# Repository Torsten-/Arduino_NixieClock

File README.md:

Arduino_NixieClock
==================

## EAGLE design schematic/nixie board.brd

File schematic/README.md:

# Teileliste

Name | Typ | Anzahl | Link
-----|------|--------| -----
. | 12V Power Supply | 1 | 
. | Einbaubuchse für Hohlstecker 5,5/2,1 | 1 | [DC 072341L](https://www.reichelt.de/einbaubuchse-aussen-5-6-mm-innen-2-1-mm-dc-072341l-p196470.html)
. | Nixie Power Supply | 1 | ebay?
N1, N2, N3, N4, N5, N6 | Nixie IN-14 | 6 | ebay?
SR50 | MCP1702-50 | 1 |  [MCP 1702-5002](https://www.reichelt.de/ldo-regler-fest-5-v-to-92-mcp-1702-5002-p90115.html)
SR33 | MCP1702-33 | 1 | [MCP 1702-3302](https://www.reichelt.de/ldo-regler-fest-3-3-v-to-92-mcp-1702-3302-p90114.html)
ESP-07/12 | ESP-07 | 1 | ebay?
IC1<br/>  | SN74141 / K155ID1<br/>IC-Sockel 16-polig | 1<br/>1 | ebay?<br/>[GS 16](https://www.reichelt.de/ic-sockel-16-polig-doppelter-federkontakt-gs-16-p8208.html)
PROG, RESET | Printtaster | 2 | [RND 210-00187](https://www.reichelt.de/printtaster-tht-1-57-n-6-x-6-x-4-3-mm-rnd-210-00187-p226408.html)
POWER | Stiftleiste RM 2,54 1x3-pol | 1 | [SL 1X40G 2,54](https://www.reichelt.de/40pol-stiftleiste-gerade-rm-2-54-sl-1x40g-2-54-p19506.html)
SERIAL | Stiftleiste RM 2,54 1x5-pol | 1 | s.o.
EXT1, EXT2 | Buchsenleiste RM 2,54 1x7-pol | 2 | [BKL 10120802](https://www.reichelt.de/buchsenleiste-36-polig-vergoldet-2-54-bkl-10120802-p235673.html)
NUMBERS<br/> <br/>  | Pfostenbuchse 10P<br/>Wannenstecker 10P<br/>Flachbandkabel 10P | 1<br/>1<br/>1 | [PFL 10](https://www.reichelt.de/pfostenbuchse-10-polig-mit-zugentlastung-pfl-10-p14571.html)<br/>[WSL 10G](https://www.reichelt.de/wannenstecker-10-polig-gerade-wsl-10g-p22816.html)<br/>[AWG 28-16G 3M](https://www.reichelt.de/flachbandkabel-awg28-16-pol-grau-3m-ring-awg-28-16g-3m-p47640.html)
DIGITS<br/> <br/>  | Pfostenbuchse 6P<br/>Wannenstecker 6P<br/>Flachbandkabel 6P | 1<br/>1<br/>1 | [PFL 6](https://www.reichelt.de/pfostenbuchse-6-polig-mit-zugentlastung-pfl-6-p53153.html)<br/>[WSL 6G](https://www.reichelt.de/wannenstecker-6-polig-gerade-wsl-6g-p85732.html)<br/>s.o.
T1, T2, T3, T4, T5, T6 | MPSA42 | 6 | [MPSA 42](https://www.reichelt.de/bipolartransistor-npn-300v-0-5a-0-625w-to-92-mpsa-42-p13112.html)
T7, T8, T9, T10, T11, T12 | MPSA92 | 6 | [MPSA 92](https://www.reichelt.de/bipolartransistor-pnp-300v-0-5a-0-625w-to-92-mpsa-92-p13119.html)
C1, C2, C3, C4 | 1 µF Ceramic | 4 | [Z5U-5 1,0µ](https://www.reichelt.de/vielschicht-keramikkondensator-1-0-20-z5u-5-1-0-p22985.html)
C5 | 100 µF Elko | 1 | [RAD 100/16](https://www.reichelt.de/elko-radial-100-f-16-v-rm-2-5-85-c-2000h-20-rad-100-16-p15101.html)
R1, R2, R3, R4, R5, R6 | 33k | 6 | [1/4W 33K](https://www.reichelt.de/widerstand-kohleschicht-33-kohm-0207-250-mw-5-1-4w-33k-p1412.html)
R7, R8, R9, R10, R11, R12 | 470k | 6 | [1/4W 470K](https://www.reichelt.de/widerstand-kohleschicht-470-kohm-0207-250-mw-5-1-4w-470k-p1433.html)
R13, R14, R15, R16, R17, R18 | 100k | 6 | [1/4W 100K](https://www.reichelt.de/widerstand-kohleschicht-100-kohm-0207-250-mw-5-1-4w-100k-p1337.html)
R19, R20 | 10k | 2 | [1/4W 10K](https://www.reichelt.de/widerstand-kohleschicht-10-kohm-0207-250-mw-5-1-4w-10k-p1338.html)
R101, R102, R103, R104, R105, R106 | 4,7k 1W | 6 | [1W 4,7K](https://www.reichelt.de/widerstand-metalloxyd-4-7-kohm-0207-1-0-w-5-1w-4-7k-p1822.html)

Bohrer für die Nixies: 19 mm

# Belegung Schieberegister
Die Pin-Belegung ist leider etwas durcheinander geraten.

Nixie Ziffer | Kabel Nummer | Schieberegister Ziffer | Schieberegister Pin | Bitmap (DCBA) | Bitmap (ABCD)
-----|-----|-----|-----|-----|-----
0 |  1 | 0 | 16 | 0000 | 0000
9 |  2 | 1 | 15 | 0001 | 1000
8 |  3 | 2 | 8 | 0010 | 0100
7 |  4 | 3 | 9 | 0011 | 1100
6 |  5 | 4 | 13 | 0100 | 0010
5 |  6 | 5 | 14 | 0101 | 1010
4 |  7 | 6 | 11 | 0110 | 0110
3 |  8 | 7 | 10 | 0111 | 1110
2 |  9 | 8 | 1 | 1000 | 0001
1 | 10 | 9 | 2 | 1001 | 1001

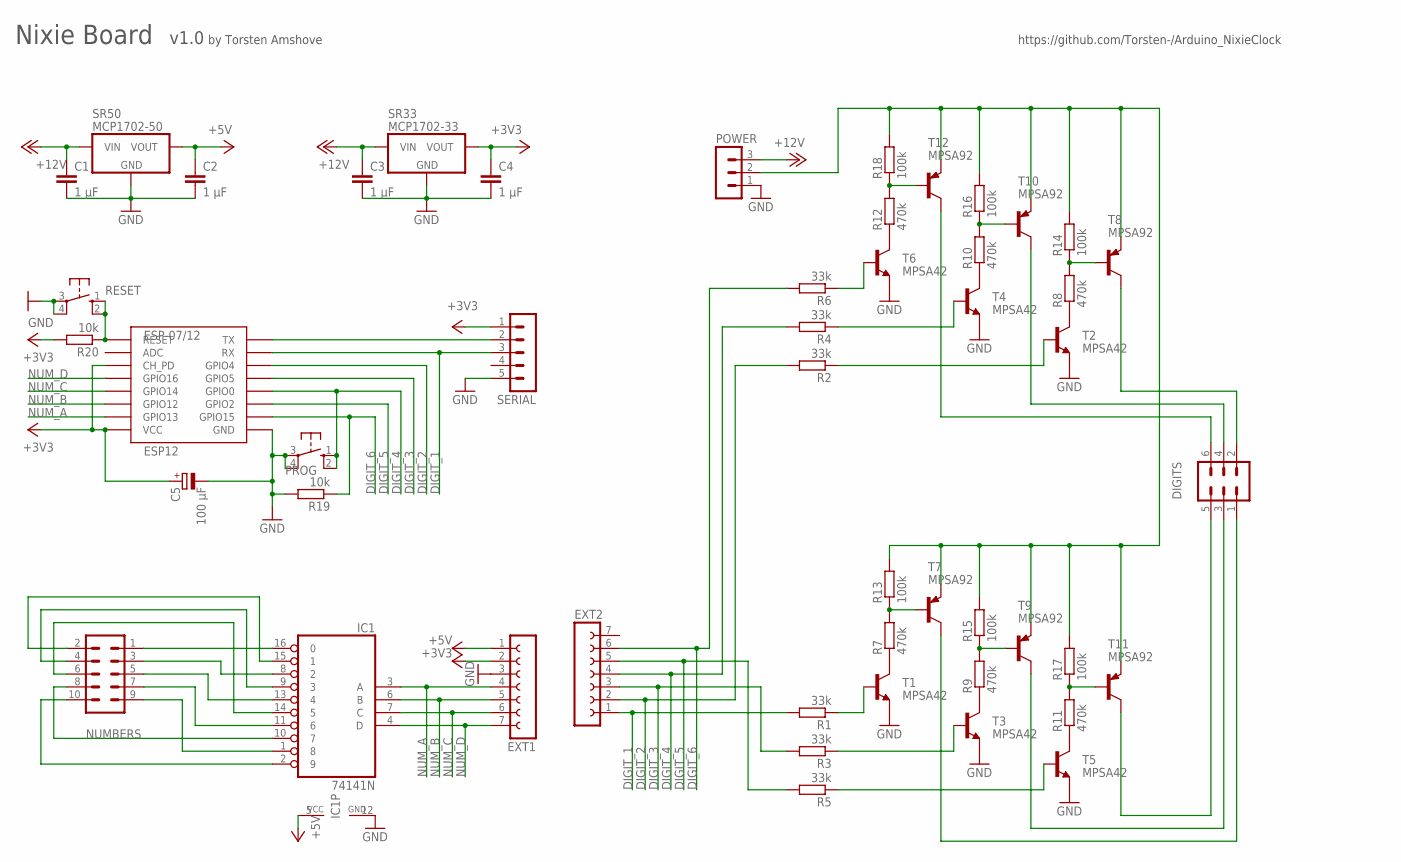
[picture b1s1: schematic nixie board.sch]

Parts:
C1, C2, C3, C4: 1 µF; C5B4.5
C5: 100 µF; E2,5-6
DIGITS: MA03-2
ESP-07/12: ESP12
EXT1, EXT2: FE07-1; FE07
IC1: 74141N; DIL16
NUMBERS: MA05-2
POWER: MA03-1
PROG: 10-XX; B3F-10XX
R1, R2, R3, R4, R5, R6: 33k; 0204/7
R7, R8, R9, R10, R11, R12: 470k; 0204/7
R13, R14, R15, R16, R17, R18: 100k; 0207/2V
R19, R20: 10k; 0204/7
RESET: 10-XX; B3F-10XX
SERIAL: MA05-1
SR33: MCP1702-33; TO-92
SR50: MCP1702-50; TO-92
T1, T2, T3, T4, T5, T6: MPSA42; TO92-EBC
T7, T8, T9, T10, T11, T12: MPSA92; TO92-EBC

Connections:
+3V3: C4.1, C5.+, ESP-07/12.CH_PD, ESP-07/12.VCC, EXT1.2, R20.2, SERIAL.1, SR33.3 (VOUT)
+5V: C2.1, EXT1.1, IC1.5 (VCC), SR50.3 (VOUT)
+12V: C1.1, C3.1, POWER.3, SR33.2 (VIN), SR50.2 (VIN)
DIGIT_1: ESP-07/12.RX, EXT2.1, R1.2, SERIAL.3
DIGIT_2: ESP-07/12.GPIO4, EXT2.2, R2.2
DIGIT_3: ESP-07/12.GPIO5, EXT2.3, R3.2
DIGIT_4: ESP-07/12.GPIO0, EXT2.4, PROG.1 (S), PROG.2 (S1), R4.2
DIGIT_5: ESP-07/12.GPIO2, EXT2.5, R5.2
DIGIT_6: ESP-07/12.GPIO15, EXT2.6, R6.2, R19.1
GND: C1.2, C2.2, C3.2, C4.2, C5.-, ESP-07/12.GND, EXT1.3, IC1.12 (GND), POWER.1, PROG.3, PROG.4 (P1), R19.2, RESET.3, RESET.4 (P1), SERIAL.5, SR33.1 (GND), SR50.1 (GND), T1.E, T2.E, T3.E, T4.E, T5.E, T6.E
unnamed: ESP-07/12.TX, SERIAL.2
unnamed: IC1.16 (0), NUMBERS.1
unnamed: IC1.15 (1), NUMBERS.2
unnamed: POWER.2, R13.2, R14.2, R15.2, R16.2, R17.2, R18.2, T7.E, T8.E, T9.E, T10.E, T11.E, T12.E
unnamed: R6.1, T6.B
unnamed: R4.1, T4.B
unnamed: R12.1, T6.C
unnamed: R12.2, R18.1, T12.B
unnamed: R2.1, T2.B
unnamed: IC1.9 (3), NUMBERS.4
unnamed: IC1.14 (5), NUMBERS.6
unnamed: R10.1, T4.C
unnamed: R10.2, R16.1, T10.B
unnamed: IC1.8 (2), NUMBERS.3
unnamed: DIGITS.6, T12.C
unnamed: R7.1, T1.C
unnamed: R8.1, T2.C
unnamed: R8.2, R14.1, T8.B
unnamed: R7.2, R13.1, T7.B
unnamed: DIGITS.4, T10.C
unnamed: DIGITS.2, T8.C
unnamed: R9.1, T3.C
unnamed: R9.2, R15.1, T9.B
unnamed: IC1.13 (4), NUMBERS.5
unnamed: R11.1, T5.C
unnamed: R11.2, R17.1, T11.B
unnamed: IC1.11 (6), NUMBERS.7
unnamed: IC1.1 (8), NUMBERS.9
unnamed: IC1.10 (7), NUMBERS.8
unnamed: R1.1, T1.B
unnamed: R3.1, T3.B
unnamed: R5.1, T5.B
unnamed: IC1.2 (9), NUMBERS.10
unnamed: ESP-07/12.RESET, R20.1, RESET.1 (S), RESET.2 (S1)
unnamed: DIGITS.5, T11.C
unnamed: DIGITS.3, T9.C
unnamed: DIGITS.1, T7.C
NUM_A: ESP-07/12.GPIO13, EXT1.4, IC1.3 (A)
NUM_B: ESP-07/12.GPIO12, EXT1.5, IC1.6 (B)
NUM_C: ESP-07/12.GPIO14, EXT1.6, IC1.7 (C)
NUM_D: ESP-07/12.GPIO16, EXT1.7, IC1.4 (D)

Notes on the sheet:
Nixie Board
v1.0
https://github.com/Torsten-/Arduino_NixieClock
by Torsten Amshove

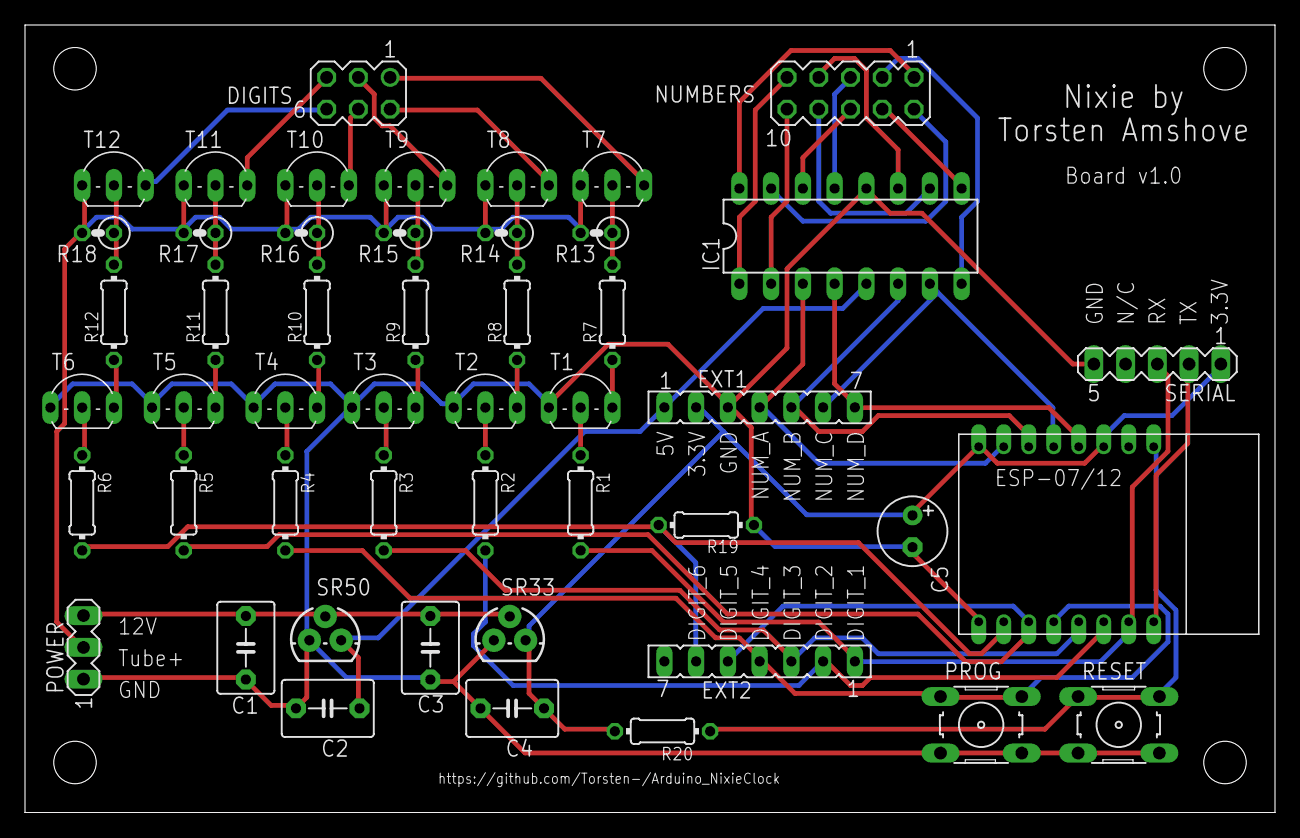
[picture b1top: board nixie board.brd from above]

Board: 2 copper layers, 100.0 x 63.0 mm, 49 parts (0 on the bottom side), 51 nets.

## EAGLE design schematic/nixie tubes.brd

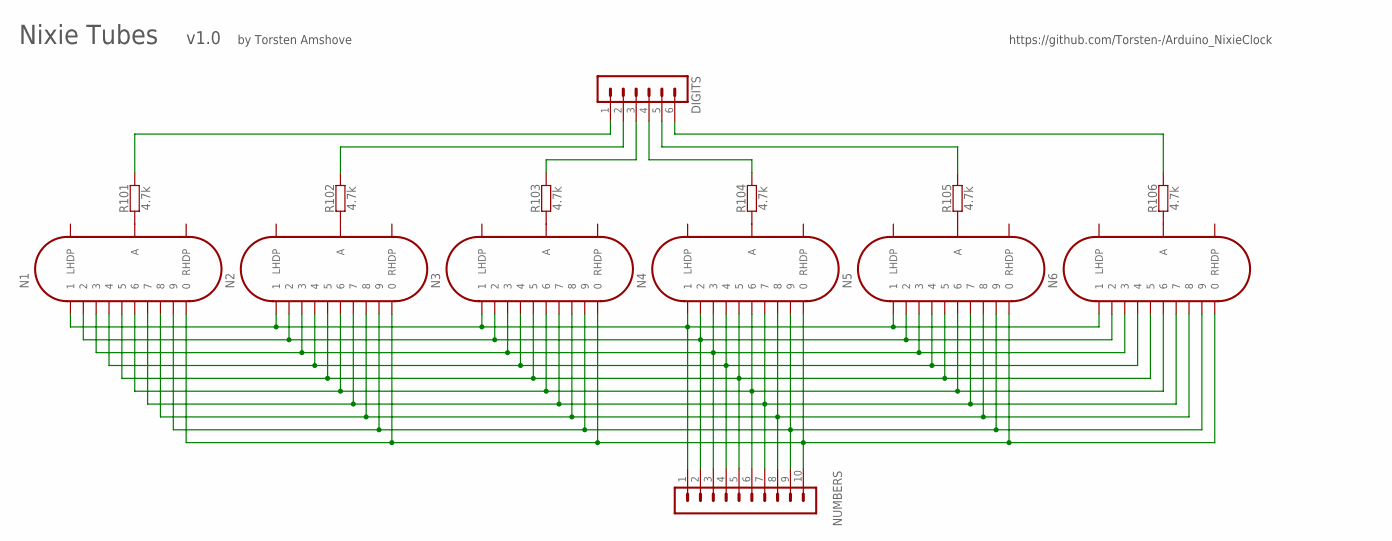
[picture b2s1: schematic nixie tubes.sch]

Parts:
DIGITS: MA06-1
N1, N2, N3, N4, N5, N6: IN-14
NUMBERS: MA10-1
R101, R102, R103, R104, R105, R106: 4.7k; R0207/10

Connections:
unnamed: N1.A, R101.1
unnamed: N2.A, R102.1
unnamed: N3.A, R103.1
unnamed: N4.A, R104.1
unnamed: N5.A, R105.1
unnamed: N6.A, R106.1
unnamed: N1.1, N2.1, N3.1, N4.1, N5.1, N6.1, NUMBERS.1
unnamed: N1.2, N2.2, N3.2, N4.2, N5.2, N6.2, NUMBERS.2
unnamed: N1.3, N2.3, N3.3, N4.3, N5.3, N6.3, NUMBERS.3
unnamed: N1.4, N2.4, N3.4, N4.4, N5.4, N6.4, NUMBERS.4
unnamed: N1.5, N2.5, N3.5, N4.5, N5.5, N6.5, NUMBERS.5
unnamed: N1.6, N2.6, N3.6, N4.6, N5.6, N6.6, NUMBERS.6
unnamed: N1.7, N2.7, N3.7, N4.7, N5.7, N6.7, NUMBERS.7
unnamed: N1.8, N2.8, N3.8, N4.8, N5.8, N6.8, NUMBERS.8
unnamed: N1.9, N2.9, N3.9, N4.9, N5.9, N6.9, NUMBERS.9
unnamed: N1.0, N2.0, N3.0, N4.0, N5.0, N6.0, NUMBERS.10
unnamed: DIGITS.1, R101.2
unnamed: DIGITS.2, R102.2
unnamed: DIGITS.3, R103.2
unnamed: DIGITS.4, R104.2
unnamed: DIGITS.5, R105.2
unnamed: DIGITS.6, R106.2

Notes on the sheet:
Nixie Tubes
v1.0
https://github.com/Torsten-/Arduino_NixieClock
by Torsten Amshove

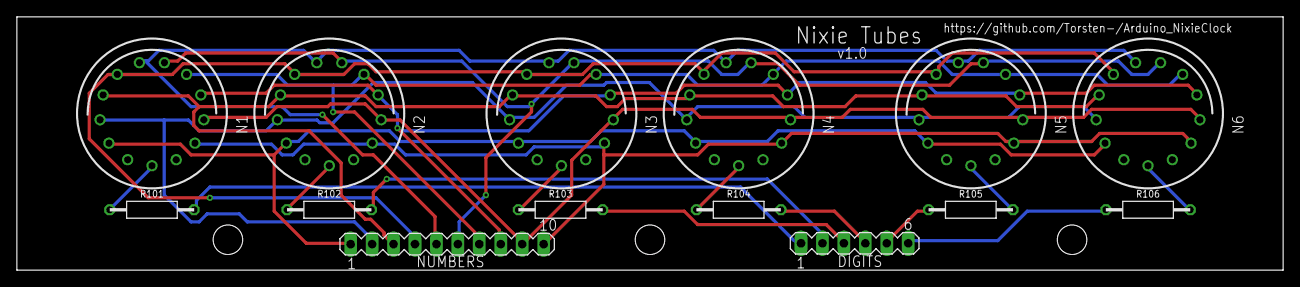
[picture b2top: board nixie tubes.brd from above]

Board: 2 copper layers, 150.0 x 30.0 mm, 14 parts (0 on the bottom side), 22 nets.

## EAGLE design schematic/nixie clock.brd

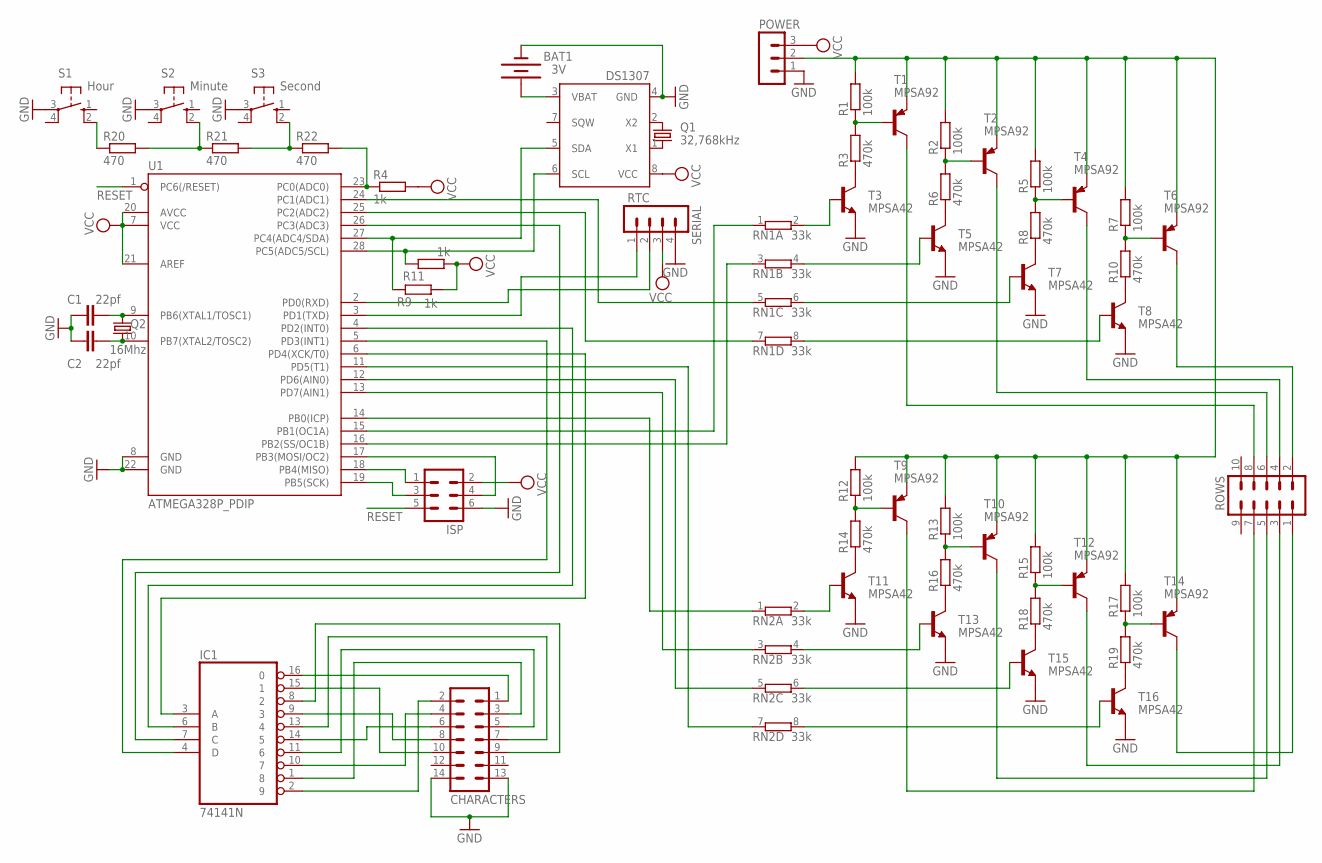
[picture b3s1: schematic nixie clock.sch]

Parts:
BAT1: 3V; BATTCOM_20MM_PTH
C1, C2: 22pf; CAP-PTH-SMALLEZ
CHARACTERS: MA07-2
IC1: 74141N; DIL16
ISP: MA03-2
POWER: MA03-1
Q1: 32,768kHz; TC26V
Q2: 16Mhz; HC49/S
R1, R2, R5, R7, R12, R13, R15, R17: 100k; 0207/2V
R3, R6, R8, R10, R14, R16, R18, R19: 470k; 0204/7
R4, R9, R11: 1k; 0204/7
R20, R21, R22: 470; 0204/7
RN1, RN2: 33k; SIL8
ROWS: MA05-2
RTC: DS1307; DIL08
S1: Hour; B3F-10XX
S2: Minute; B3F-10XX
S3: Second; B3F-10XX
SERIAL: MA04-1
T1, T2, T4, T6, T9, T10, T12, T14: MPSA92; TO92-EBC
T3, T5, T7, T8, T11, T13, T15, T16: MPSA42; TO92-EBC
U1: ATMEGA328P_PDIP; DIL28-3

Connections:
GND: BAT1.2 (-), C1.1, C2.1, CHARACTERS.13, CHARACTERS.14, IC1.12 (GND), ISP.6, POWER.1, RTC.4 (GND), S1.3, S2.3, S3.3, SERIAL.4, T3.E, T5.E, T7.E, T8.E, T11.E, T13.E, T15.E, T16.E, U1.8 (GND), U1.22 (GND)
unnamed: RN1.2, T3.B
unnamed: R3.1, T3.C
unnamed: R1.1, R3.2, T1.B
unnamed: POWER.2, R1.2, R2.2, R5.2, R7.2, R12.2, R13.2, R15.2, R17.2, T1.E, T2.E, T4.E, T6.E, T9.E, T10.E, T12.E, T14.E
unnamed: RN1.4 (2), T5.B
unnamed: RN1.6 (2), T7.B
unnamed: R6.1, T5.C
unnamed: R2.1, R6.2, T2.B
unnamed: RN1.8 (2), T8.B
unnamed: ROWS.8, T1.C
unnamed: R14.1, T11.C
unnamed: R8.1, T7.C
unnamed: R5.1, R8.2, T4.B
unnamed: R12.1, R14.2, T9.B
unnamed: ROWS.6, T2.C
unnamed: R16.1, T13.C
unnamed: R10.1, T8.C
unnamed: R7.1, R10.2, T6.B
unnamed: R13.1, R16.2, T10.B
unnamed: ROWS.4, T4.C
unnamed: ROWS.2, T6.C
unnamed: R18.1, T15.C
unnamed: R15.1, R18.2, T12.B
unnamed: R20.1, S1.2 (S1)
unnamed: R19.1, T16.C
unnamed: R17.1, R19.2, T14.B
unnamed: R20.2, R21.1, S2.2 (S1)
unnamed: R21.2, R22.1, S3.2 (S1)
unnamed: RN2.2, T11.B
unnamed: RN2.4 (2), T13.B
unnamed: RN2.6 (2), T15.B
unnamed: RN2.8 (2), T16.B
unnamed: CHARACTERS.1, IC1.16 (0)
unnamed: CHARACTERS.3, IC1.1 (8)
unnamed: CHARACTERS.5, IC1.11 (6)
unnamed: CHARACTERS.7, IC1.13 (4)
unnamed: CHARACTERS.9, IC1.8 (2)
unnamed: CHARACTERS.2, IC1.2 (9)
unnamed: CHARACTERS.4, IC1.10 (7)
unnamed: CHARACTERS.6, IC1.14 (5)
unnamed: CHARACTERS.8, IC1.9 (3)
unnamed: CHARACTERS.10, IC1.15 (1)
unnamed: C1.2, Q2.2, U1.9 (PB6(XTAL1/TOSC1))
unnamed: ISP.3, U1.19 (PB5(SCK))
unnamed: ISP.1, U1.18 (PB4(MISO))
unnamed: ISP.4, U1.17 (PB3(MOSI/OC2))
unnamed: R9.2, RTC.5 (SDA), U1.27 (PC4(ADC4/SDA))
unnamed: R11.2, RTC.6 (SCL), U1.28 (PC5(ADC5/SCL))
unnamed: Q1.2, RTC.2 (X2)
unnamed: Q1.1, RTC.1 (X1)
unnamed: C2.2, Q2.1, U1.10 (PB7(XTAL2/TOSC2))
unnamed: RN2.7 (1), U1.11 (PD5(T1))
unnamed: IC1.7 (C), U1.26 (PC3(ADC3))
unnamed: IC1.4 (D), U1.5 (PD3(INT1))
unnamed: IC1.3 (A), U1.6 (PD4(XCK/T0))
unnamed: IC1.6 (B), U1.4 (PD2(INT0))
unnamed: RN2.5 (1), U1.12 (PD6(AIN0))
unnamed: RN2.3 (1), U1.13 (PD7(AIN1))
unnamed: RN2.1, U1.14 (PB0(ICP))
unnamed: RN1.1, U1.15 (PB1(OC1A))
unnamed: RN1.3 (1), U1.16 (PB2(SS/OC1B))
unnamed: RN1.5 (1), U1.24 (PC1(ADC1))
unnamed: RN1.7 (1), U1.25 (PC2(ADC2))
unnamed: R4.1, R22.2, U1.23 (PC0(ADC0))
unnamed: BAT1.1 (+), RTC.3 (VBAT)
unnamed: SERIAL.2, U1.2 (PD0(RXD))
unnamed: SERIAL.1, U1.3 (PD1(TXD))
unnamed: ROWS.1, T14.C
unnamed: ROWS.3, T12.C
unnamed: ROWS.5, T10.C
unnamed: ROWS.7, T9.C
RESET: ISP.5, U1.1 (PC6(/RESET))
VCC: IC1.5 (VCC), ISP.2, POWER.3, R4.2, R9.1, R11.1, RTC.8 (VCC), SERIAL.3, U1.7 (VCC), U1.20 (AVCC), U1.21 (AREF)

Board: 2 copper layers, 56 parts (0 on the bottom side), 74 nets, no tracks yet.

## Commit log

2015-01-04 Initial Code
2015-01-07 Kleine fixes und Funktion fuer Buttons
2015-01-07 Schaltplan added
2016-02-06 Echtzeituhr angebunden
2016-08-13 Uhrzeit ging zu langsam
2016-08-22 Changed Lib
2019-05-02 Schaltplan aktualisiert
2019-05-06 Changed to ESP8266 with NTP
2019-05-10 SofAP and Webserver
2019-05-11 first Final WiFi Version
2019-05-13 Viewport for mobile devices
2019-05-17 Disable AP
2019-10-28 Board Layout
2019-10-28 Layout fix
2019-10-29 added reset and elko
2019-11-22 v1.0
2019-11-22 BoM aktualisiert
2020-03-08 Pin-Belegung
2020-03-08 Code angepasst zu neuem Board
2020-03-13 Bohrschablone für CNC

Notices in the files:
parts and their libraries:
SparkFun-DigitalIC: Licensing: Creative Commons ShareAlike 4.0 International - https://creativecommons.org/licenses/by-sa/4.0
